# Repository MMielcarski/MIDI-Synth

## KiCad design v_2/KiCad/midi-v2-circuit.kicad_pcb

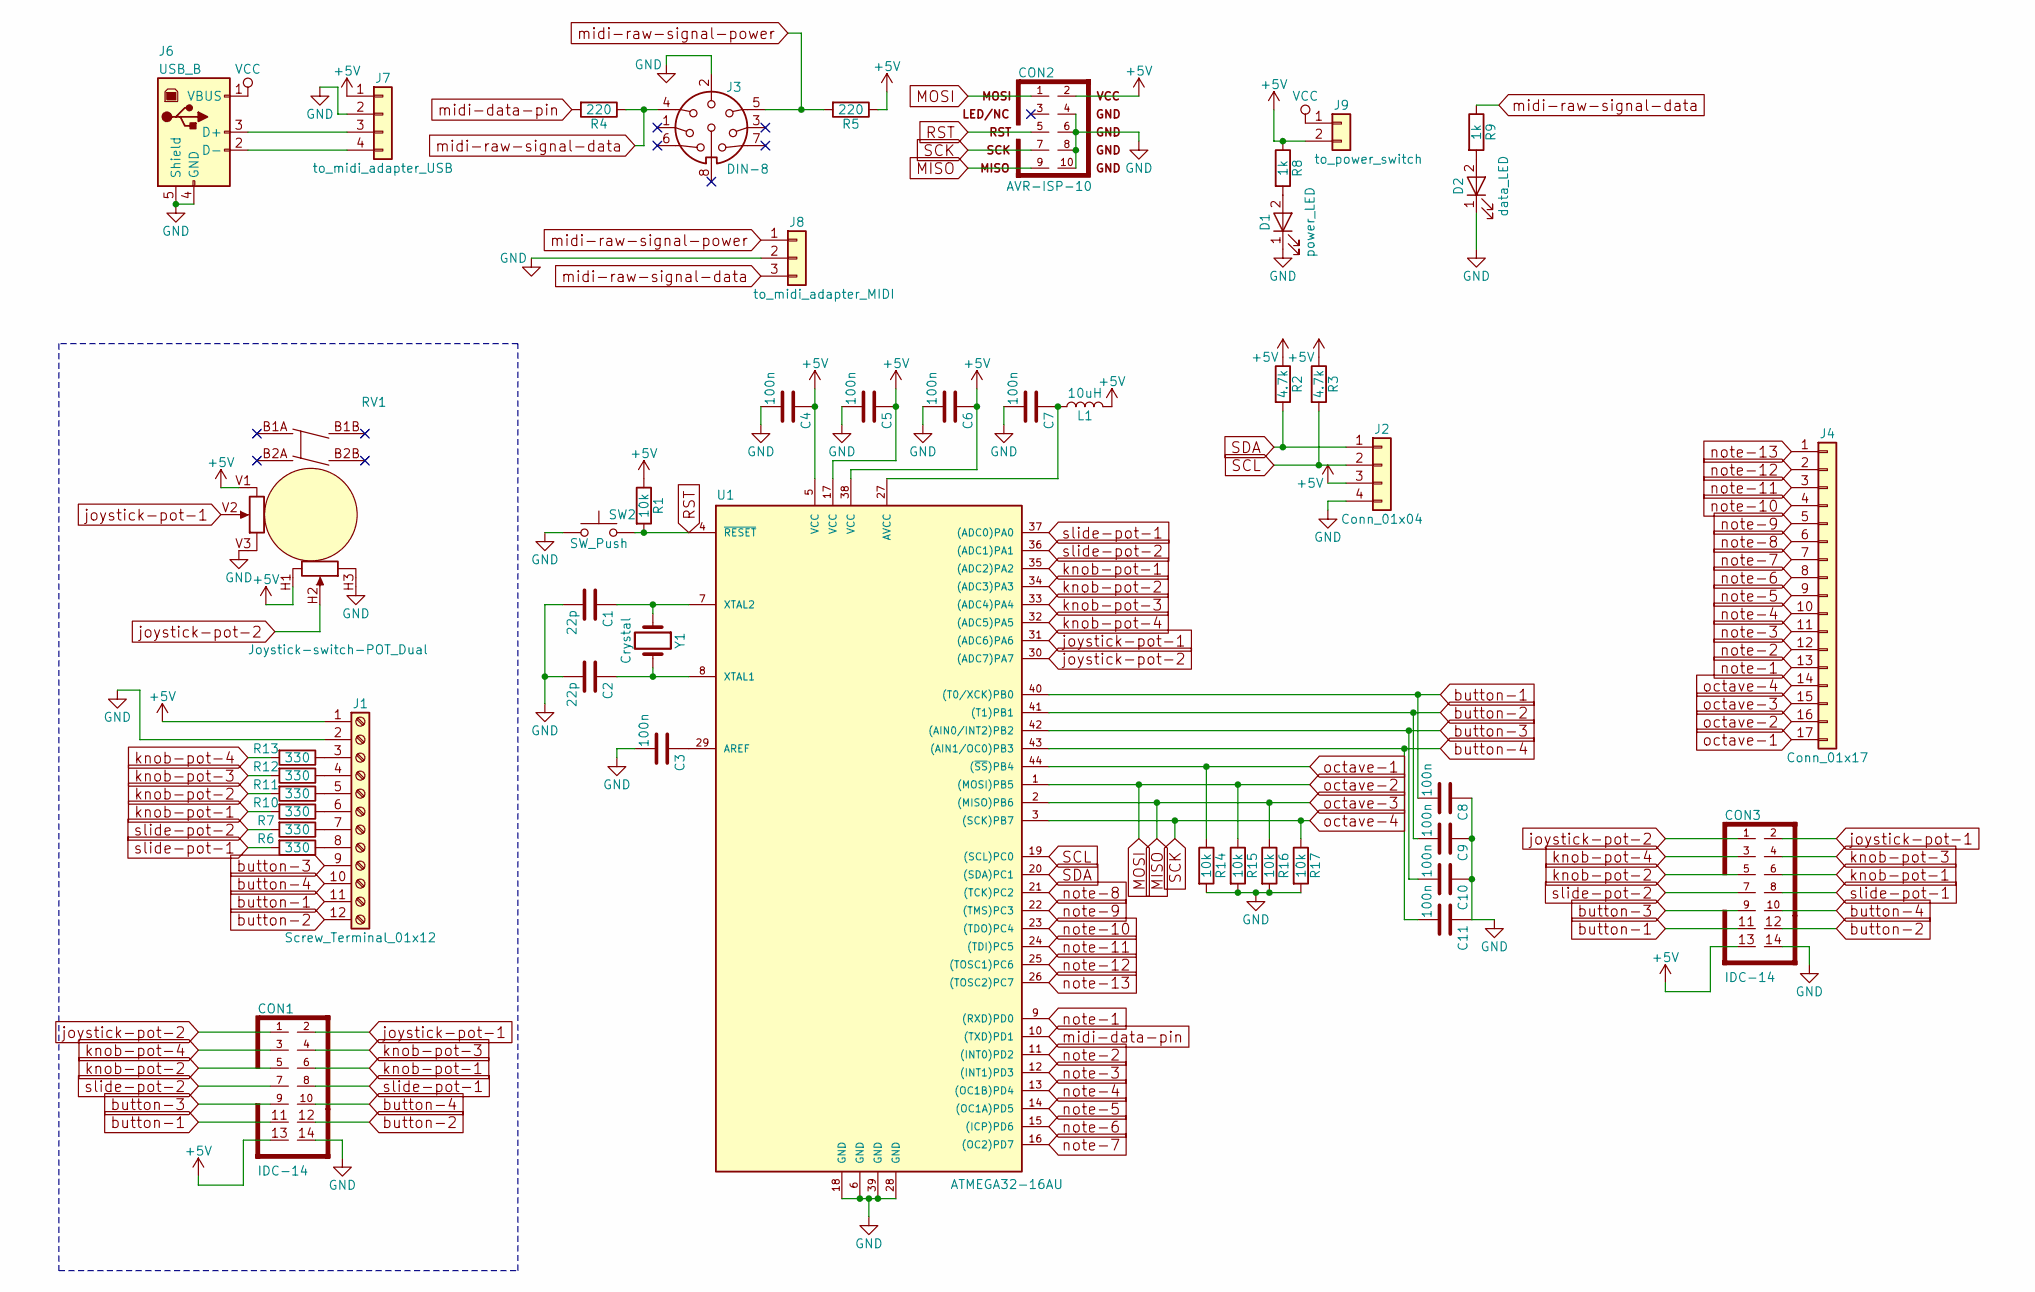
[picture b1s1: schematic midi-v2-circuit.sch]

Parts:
C1, C2: 22p; C_0805_HandSoldering
C3, C4, C5, C6, C7, C8, C9, C10, C11: 100n; C_0805_HandSoldering
CON1: IDC-14; IDC-Header_2x07_Pitch2.54mm_Angled
CON2: AVR-ISP-10; IDC-Header_2x05_Pitch2.54mm_Angled
CON3: IDC-14; IDC-Header_2x07_Pitch2.54mm_Straight
D1: power_LED; LED_D3.0mm
D2: data_LED; LED_D3.0mm
J1: Screw_Terminal_01x12; TerminalBlock_Phoenix_MPT-2.54mm_12pol
J2: Conn_01x04; Pin_Header_Straight_1x04_Pitch2.54mm
J3: DIN-8; MIDI-DIN-8
J4: Conn_01x17; IDC-Header_2x10_Pitch2.54mm_Angled
J6: USB_B
J7: to_midi_adapter_USB; Pin_Header_Straight_1x04_Pitch2.54mm
J8: to_midi_adapter_MIDI; Pin_Header_Straight_1x03_Pitch2.54mm
J9: to_power_switch; Pin_Header_Straight_1x02_Pitch2.54mm
L1: 10uH; L_0805_HandSoldering
R1, R14, R15, R16, R17: 10k; R_0805_HandSoldering
R2, R3: 4.7k; R_0805_HandSoldering
R4, R5: 220; R_0805_HandSoldering
R6, R7, R10, R11, R12, R13: 330; R_0805_HandSoldering
R8, R9: 1k; R_0805_HandSoldering
RV1: Joystick-switch-POT_Dual; JOYSTICK
SW2: SW_Push; SW_Tactile_Straight_KSA0Axx1LFTR
U1: ATMEGA32-16AU; LQFP-44_10x10mm_Pitch0.8mm
Y1: Crystal; Crystal_HC18-U_Vertical

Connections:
+5V: C4.1, C5.1, C6.1, CON1.13, CON2.2, CON3.13, J1.1, J2.3, J7.1, J9.2, L1.2, R1.1, R2.1, R3.1, R5.1, R8.1, RV1.H1, RV1.V1, U1.5 (VCC), U1.17 (VCC), U1.38 (VCC)
GND: C1.2, C2.2, C3.2, C4.2, C5.2, C6.2, C7.2, C8.1, C9.1, C10.1, C11.1, CON1.14, CON2.4, CON2.6, CON2.8, CON2.10, CON3.14, D1.1 (K), D2.1 (K), J1.2, J2.4, J3.2, J6.4 (GND), J6.5 (Shield), J7.2, J8.2, R14.2, R15.2, R16.2, R17.2, RV1.H3, RV1.V3, SW2.1, U1.6 (GND), U1.18 (GND), U1.28 (GND), U1.39 (GND)
MISO: CON2.9, J4.15, R16.1, U1.2 ((MISO)PB6)
MOSI: CON2.1, J4.16, R15.1, U1.1 ((MOSI)PB5)
unnamed: C1.1, U1.7 (XTAL2), Y1.1
unnamed: C2.1, U1.8 (XTAL1), Y1.2
unnamed: C3.1, U1.29 (AREF)
unnamed: C7.1, L1.1, U1.27 (AVCC)
unnamed: D1.2 (A), R8.2
unnamed: D2.2 (A), R9.2
unnamed: J1.3, R13.1
unnamed: J1.4, R12.1
unnamed: J1.5, R11.1
unnamed: J1.6, R10.1
unnamed: J1.7, R7.1
unnamed: J1.8, R6.1
unnamed: J6.2 (D-), J7.4
unnamed: J6.3 (D+), J7.3
RST: CON2.5, R1.2, SW2.2, U1.4 (~RESET)
SCK: CON2.7, J4.14, R17.1, U1.3 ((SCK)PB7)
SCL: J2.2, R3.2, U1.19 ((SCL)PC0)
SDA: J2.1, R2.2, U1.20 ((SDA)PC1)
VCC: J6.1 (VBUS), J9.1
button-1: C8.2, CON1.11, CON3.11, J1.11, U1.40 ((T0/XCK)PB0)
button-2: C9.2, CON1.12, CON3.12, J1.12, U1.41 ((T1)PB1)
button-3: C10.2, CON1.9, CON3.9, J1.9, U1.42 ((AIN0/INT2)PB2)
button-4: C11.2, CON1.10, CON3.10, J1.10, U1.43 ((AIN1/OC0)PB3)
joystick-pot-1: CON1.2, CON3.2, RV1.V2, U1.31 ((ADC6)PA6)
joystick-pot-2: CON1.1, CON3.1, RV1.H2, U1.30 ((ADC7)PA7)
knob-pot-1: CON1.6, CON3.6, R10.2, U1.35 ((ADC2)PA2)
knob-pot-2: CON1.5, CON3.5, R11.2, U1.34 ((ADC3)PA3)
knob-pot-3: CON1.4, CON3.4, R12.2, U1.33 ((ADC4)PA4)
knob-pot-4: CON1.3, CON3.3, R13.2, U1.32 ((ADC5)PA5)
midi-data-pin: R4.2, U1.10 ((TXD)PD1)
midi-raw-signal-data: J3.4, J8.3, R4.1, R9.1
midi-raw-signal-power: J3.5, J8.1, R5.2
note-1: J4.13, U1.9 ((RXD)PD0)
note-2: J4.12, U1.11 ((INT0)PD2)
note-3: J4.11, U1.12 ((INT1)PD3)
note-4: J4.10, U1.13 ((OC1B)PD4)
note-5: J4.9, U1.14 ((OC1A)PD5)
note-6: J4.8, U1.15 ((ICP)PD6)
note-7: J4.7, U1.16 ((OC2)PD7)
note-8: J4.6, U1.21 ((TCK)PC2)
note-9: J4.5, U1.22 ((TMS)PC3)
note-10: J4.4, U1.23 ((TDO)PC4)
note-11: J4.3, U1.24 ((TDI)PC5)
note-12: J4.2, U1.25 ((TOSC1)PC6)
note-13: J4.1, U1.26 ((TOSC2)PC7)
octave-1: J4.17, R14.1, U1.44 ((~SS~)PB4)
slide-pot-1: CON1.8, CON3.8, R6.2, U1.37 ((ADC0)PA0)
slide-pot-2: CON1.7, CON3.7, R7.2, U1.36 ((ADC1)PA1)

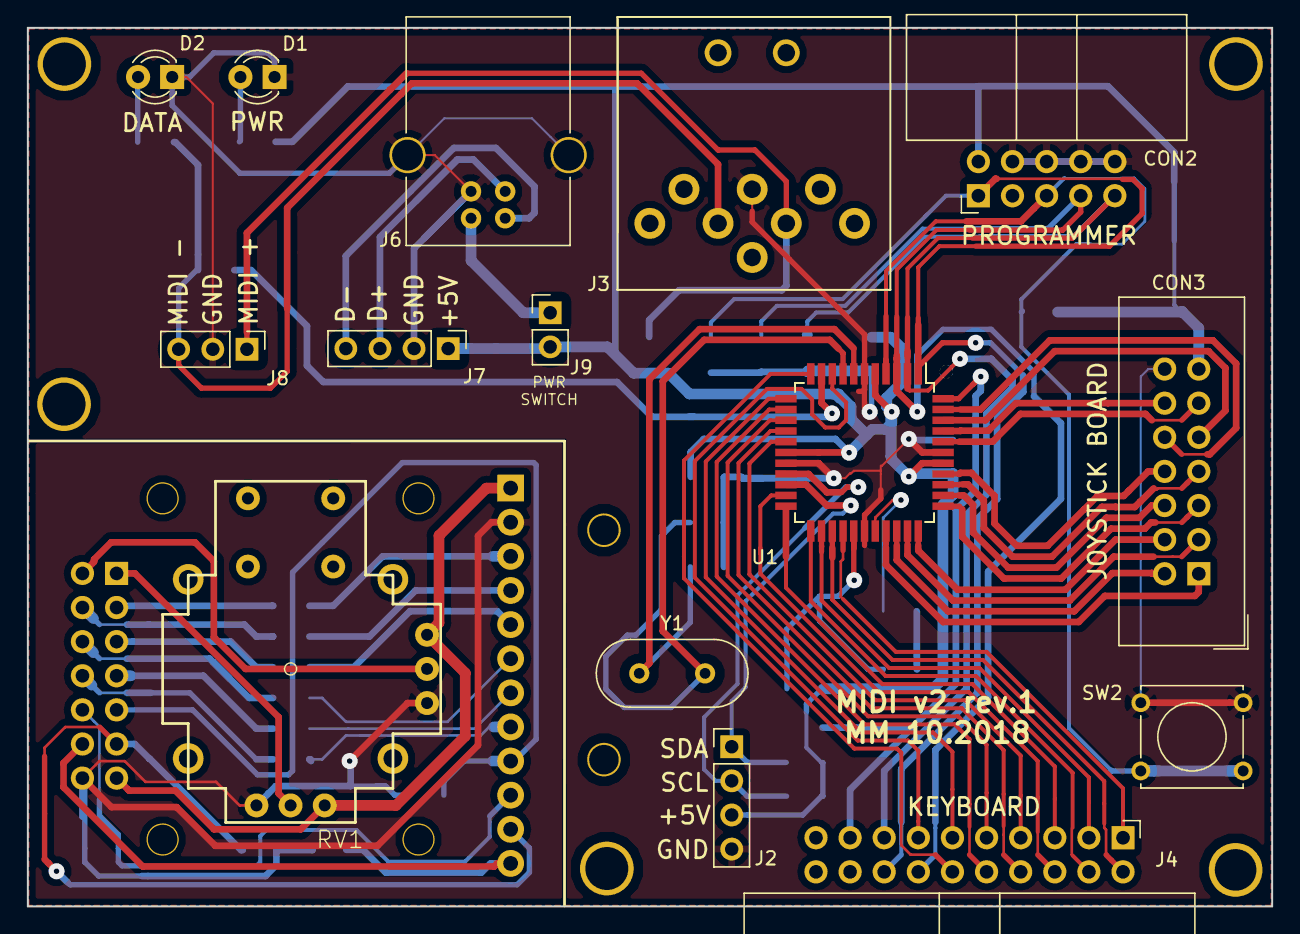
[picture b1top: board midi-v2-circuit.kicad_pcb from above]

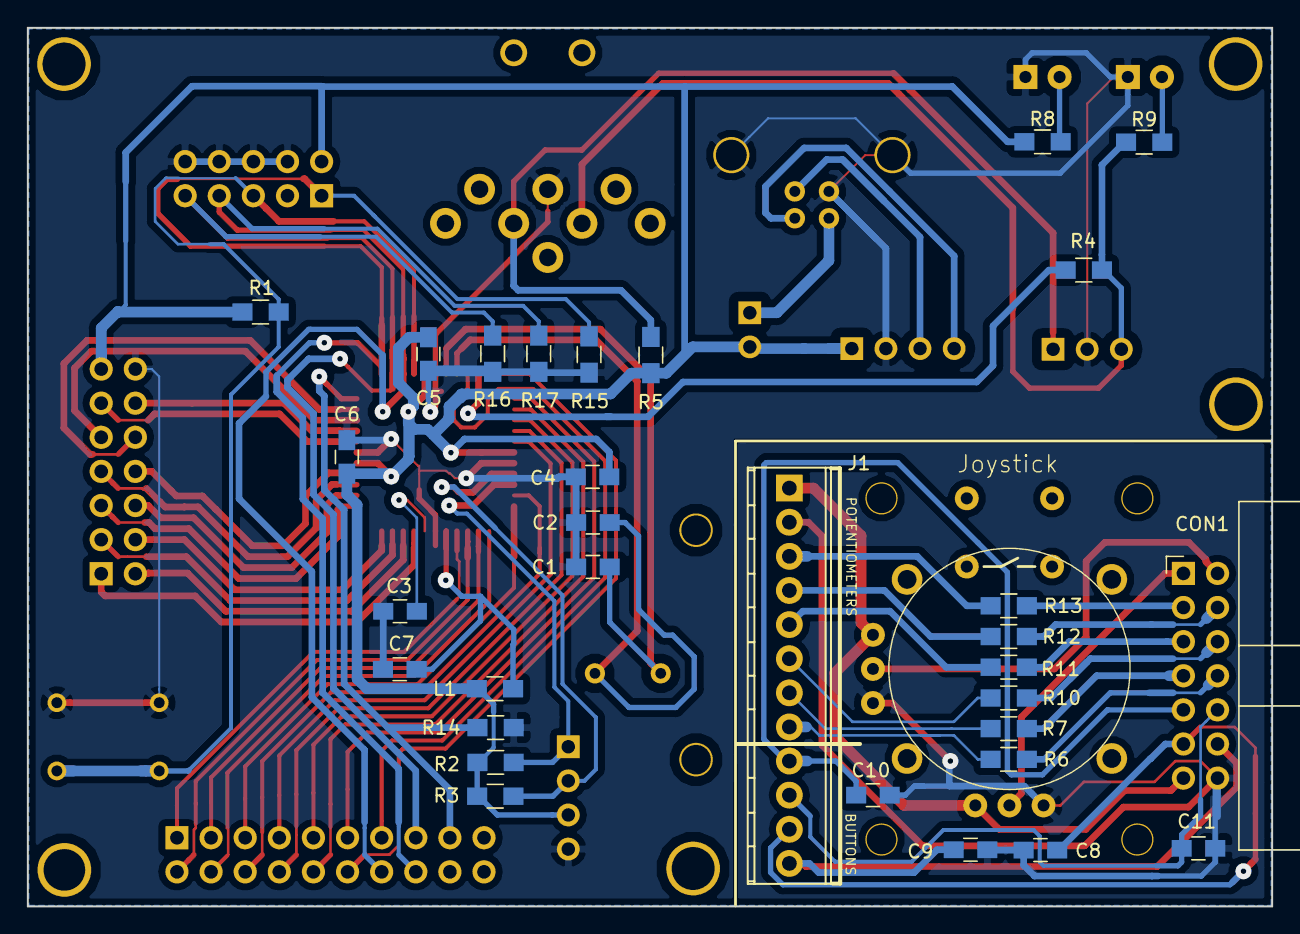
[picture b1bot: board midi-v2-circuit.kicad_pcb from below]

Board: 2 copper layers, 92.6 x 65.4 mm, 46 parts (32 on the bottom side), 52 nets.

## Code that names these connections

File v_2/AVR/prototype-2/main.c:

// device: 	AtMega 32
// author:  Maciej Mielcarski
// Midi v2

#define F_CPU 16000000UL
#include <avr/io.h>
#include <avr/interrupt.h>
//#define BAUD 9600 
#define BAUD 31250
#define MYUBRR F_CPU/16/BAUD-1	// ubrr = 31(MIDI) 113(9600) normal asynch. mode
#include <util/setbaud.h>
#define TIM1_PSC 1024		// TIMER 1 prescaler value
#define TIM1_PER 10		// TIMER 1 desired period in miliseconds

#define NOTE_ON_CMD 0x90
#define NOTE_OFF_CMD 0x80
#define CC_CMD 0xB0

#define PITCH_BEND_CMD 0xE0
#define MODULATION_WHEEL_CMD 0x01
#define BREATH_CONTROLLER_CMD 0x02
#define MAIN_VOLUME_CMD 0x07	
#define GEN_PURP_CTRL_1_CMD 0x10
#define GEN_PURP_CTRL_2_CMD 0x11
#define GEN_PURP_CTRL_3_CMD 0x12
#define GEN_PURP_CTRL_4_CMD 0x13

#define SOUND_CTRL_6_DECAY_CMD 0x4B

#define VEL_DEF_CMD		0x40	// default 64 velocity

#define UNDEF_1 0x14
#define UNDEF_2 0x15
#define UNDEF_3 0x16
#define UNDEF_4 0x17
#define UNDEF_5 0x18
#define UNDEF_6 0x19
#define UNDEF_7 0x1A
#define UNDEF_8 0x19

#define CC_ON_VAL 0x46
#define CC_OFF_VAL 0x3C

#define note1 PD0 
#define note2 PD2 
#define note3 PD3 
#define note4 PD4 
#define note5 PD5 
#define note6 PD6 
#define note7 PD7 
#define note8 PC2 
#define note9 PC3 
#define note10 PC4 
#define note11 PC5 
#define note12 PC6 
#define note13 PC7 

#define octave1 PB4 
#define octave2 PB5 
#define octave3 PB6 
#define octave4 PB7 

#define button_pin_port PINB 
#define button1 PB0
#define button2 PB1
#define button3 PB2
#define button4 PB3

int NOTES_tab[13] = {note1,note2,note3,note4,note5,note6,note7,note8,note9,note10,note11,note12,note13};
int OCTAVES_tab[4] = {octave1,octave2,octave3,octave4};
int PRESSED_KEY_tab[13][4]={0};

int BUTTON_tab = {button1, button2, button3, button4};
int PRESSED_BUTTON_tab[4] = {};
unsigned int PRESSED_BUTTON_STATE_tab[4] = {};

int adc_read[8] = {};
int adc_prev_read[8] = {};	

const float EMA_a = 0.6;
int EMA[8] = {};
int EMA_prev[8] = {};

int octave_change = 3;

// ------------------------- TIMER ----------------------------------------
void TIM1_Init(void)	// enable interrupts
{
    OCR1A = (((F_CPU/1000) / TIM1_PSC) * TIM1_PER) - 1;	// counter size
    TCCR1B |= (1 << WGM12);							// Mode 4, CTC on OCR1A
    TIMSK |= (1 << OCIE1A);						// Set interrupt on compare match	
    TCCR1B |= (1 << CS12) | (1 << CS10);			// set prescaler to 1024 and start the timer
    sei();	
}

// ------------------------- USART ----------------------------------------
void USART_Init(unsigned int ubrr)		
{
   UBRRH = (unsigned char)(ubrr>>8);	// set baud rate to 31250
   UBRRL = (unsigned char)ubrr;		//
   UCSRB = (1<<TXEN);		// Enable transmitter 
   UCSRC = (1<<URSEL)|(1<<USBS)|(3<<UCSZ0);		// Set frame format: 8data, 2stop bit
}

void uart_putchar(char c) 
{
	while ( !(UCSRA & (1<<UDRE)) )	// Wait for empty transmit buffer 
	;
    UDR = c;							// Put data into buffer, sends the data 
}

void uart_putstring(char tab[])
{
	int i =0;
	while (( UCSRA & (1<<UDRE))  == 0){};
        while (tab[i] != 0x00)
		{ 
            uart_putchar(tab[i]);
			i++; 
        }
}

void uart_putint(int value)
{
	char tab[16];
	itoa(value,tab,10);
	uart_putstring(tab);
}

// ------------------------- ADC ----------------------------------------
void ADC_Init(void)
{
	ADCSRA |= (1 << ADPS2) | (1 << ADPS1) | (1 << ADPS0); // Set ADC prescaler to 128 - 125KHz sample rate @ 16MHz
	ADMUX |= (1 << REFS0); 	// Set ADC reference to AVCC
	ADCSRA |= (1 << ADEN);  // Enable ADC
}

uint16_t ADC_read(uint8_t channel)		
{
	channel &= 0x07;					// AND operation with 7 (will keep channel between 0-7) 
	ADMUX = (ADMUX & 0xF8) | channel;	// clears 3 first bits before OR
	ADCSRA |= (1 << ADSC);				// start single convesrion
	while(ADCSRA & (1 << ADSC));		// wait for conversion to complete
	return ADCW;
}
// ------------------------- OTHER ----------------------------------------

void PORT_Init(void)
{
	MCUCSR = (1<<JTD);			//disabling JTAG
	MCUCSR = (1<<JTD);			//
	DDRD = 0xFF;
	DDRC = 0xFF;
	
	PORTB |= (1<<button1)|(1<<button2)|(1<<button3)|(1<<button4);	// pull-up on buttons
}

void note_on(int key, int oct)
{
	uart_putchar(NOTE_ON_CMD);		// note on
	uart_putchar(key + (oct+octave_change) * 12);
	uart_putchar(VEL_DEF_CMD);
}

void note_off(int key, int oct)
{
	uart_putchar(NOTE_OFF_CMD);		// note off
	uart_putchar(key + (oct+octave_change) * 12);
	uart_putchar(VEL_DEF_CMD);
}

int button_pressed(int pin_port, int pin)
{
	if(!(pin_port & (1<<pin)) )
		return 1;
	else 
		return 0;
}

void CC_send_BUTTON(uint8_t data1, uint8_t data2, int button_pin)
{
	if(button_pressed(button_pin_port,button_pin) && !(PRESSED_BUTTON_tab[button_pin]))
	{
		PRESSED_BUTTON_tab[button_pin] = 1;
		uart_putchar(CC_CMD);
		if(PRESSED_BUTTON_STATE_tab[button_pin])
		{
			PRESSED_BUTTON_STATE_tab[button_pin] = 0;
			uart_putchar(data1);		
			uart_putchar(CC_OFF_VAL);	
		}
		else
		{
			PRESSED_BUTTON_STATE_tab[button_pin] = 1;
			uart_putchar(data1);		
			uart_putchar(CC_ON_VAL);
		}	
	}
	else if(!(button_pressed(button_pin_port,button_pin)))
	{
		PRESSED_BUTTON_tab[button_pin] = 0;
	}
}

void CC_send_ADC(uint8_t control_num,  unsigned int channel)
{
	adc_prev_read[channel] = adc_read[channel];
	int adc_sum = 0;
	for(int i=0;i<16;i++)
	{
		adc_sum += ADC_read(channel);
	}
	adc_read[channel] = adc_sum/16;

	uint8_t adc_7bit = (adc_read[channel] >> 3);
	uint8_t adc_prev_7bit = (adc_prev_read[channel] >> 3);

	if((int)adc_7bit != (int)adc_prev_7bit)
	{
		EMA_prev[channel] = EMA[channel];
		EMA[channel] = (EMA_a*adc_7bit) + (1-EMA_a)*adc_prev_7bit;
		if(EMA[channel] != EMA_prev[channel])
		{
			uart_putchar(CC_CMD);
			uart_putchar(control_num);
			uart_putchar(EMA[channel]);
		}
	}
}

ISR(TIMER1_COMPA_vect)	// timer1 overflow interrupt
{
		CC_send_BUTTON(UNDEF_1,1,button1);	// todo: tab with pin numbers
		CC_send_BUTTON(UNDEF_2,1,button2);
		CC_send_BUTTON(UNDEF_3,1,button3);
		CC_send_BUTTON(UNDEF_4,1,button4);

	// octave change:
	/*if(button_pressed(button_pin_port,button3) && !(PRESSED_BUTTON_tab[button3]))
	{
		octave_change++;
	}
	else if(!(button_pressed(button_pin_port,button3)))
	{
		PRESSED_BUTTON_tab[button3] = 0;
	}

	if(button_pressed(button_pin_port,button4) && !(PRESSED_BUTTON_tab[button4]))
	{
		if(octave_change > 0)
		octave_change--;
	}
	else if(!(button_pressed(button_pin_port,button4)))
	{
		PRESSED_BUTTON_tab[button4] = 0;
	}*/

		CC_send_ADC(UNDEF_5, 0);	// slide 1
		CC_send_ADC(UNDEF_6, 1);	// slide 2
		CC_send_ADC(GEN_PURP_CTRL_1_CMD, 2);	// knob 1 
		CC_send_ADC(GEN_PURP_CTRL_2_CMD, 3);	// knob 2
		CC_send_ADC(GEN_PURP_CTRL_3_CMD, 4);	// knob 3
		CC_send_ADC(GEN_PURP_CTRL_4_CMD, 5);	// knob 4		
		CC_send_ADC(UNDEF_7, 6);	// joystick 1	
		CC_send_ADC(UNDEF_8, 7);	// joystick 2	

for(int i=0; i<13; i++)		// notes loop
		{
			if(i < 7)	// PORTD
			{
				PORTD |= (1<<NOTES_tab[i]);
			}
			else		// PORTC
			{
				PORTC |= (1<<NOTES_tab[i]);
			}

			// if(i == 12)		// last key case
			// {
			// 	if(PINC & (1<<NOTES_tab[12]) && !(PRESSED_KEY_tab[12][0]) )
			// 	{
			// 		PRESSED_KEY_tab[12][0] = 1;
			// 		note_on(12,0);
			// 	}
			// 	else if( !(PINC & (1<<NOTES_tab[12])) && PRESSED_KEY_tab[12][0])
			// 	{
			// 		PRESSED_KEY_tab[12][0] = 0;
			// 		note_off(12,0);
			// 	}
			// }

			for(int j=0; j<4; j++)		// octaves loop
			{
				if( PINB & (1<<OCTAVES_tab[j]) && !(PRESSED_KEY_tab[i][j]) )
				{
					PRESSED_KEY_tab[i][j] = 1;
					note_on(i,j);
				}
				else if( !(PINB & (1<<OCTAVES_tab[j])) && PRESSED_KEY_tab[i][j] )
				{
					PRESSED_KEY_tab[i][j] = 0;
					note_off(i,j);
				}
			}
			
			if(i < 7)	// PORTD
			{
				PORTD &= ~(1<<NOTES_tab[i]);
			}
			else		// PORT C
			{
				PORTC &= ~(1<<NOTES_tab[i]);
			}
		}
}

// ------------------------- MAIN ----------------------------------------

int main(void)
{
	USART_Init(MYUBRR);
	PORT_Init();
	ADC_Init();
	TIM1_Init();

	while(1)
	{

	}
}

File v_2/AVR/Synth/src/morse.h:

#ifndef MORSE_H_
#define MORSE_H_

#define F_CPU 1000000UL
#include <avr/io.h>
#include "HD44780.h"
#include <util/delay.h>
#include <stdio.h>
#include <stdlib.h> 
#include <avr/interrupt.h>

#define ENC_BTN PA3
#define ENC_A PA1
#define ENC_B PA2
#define LED PC4
#define SW_1 PC1
#define SW_2 PC2

	extern int encoderCount;	//encoder turns
	extern uint8_t val;			//encoder actual gray code reading
	extern int asciiNum;		//ascii value of currently displayed character
	extern char userInput[];
	extern volatile uint16_t Timer1, Timer2;
	extern int flag;

	void delay_ms( int ms);
	uint8_t readEncoder(void);
	void initializeSetup (void);
	void readEncoderCounter (void);
	void broadcast(int period,int length);
	void LCD_clearLine(int nr);
	int dial(void);
	void messageDisplay(void);
	int isButton(void);
	void LCD_move(char dir);
	void LCD_moveMode(void);
	void blinkLed(int on, int off);
	int messageDecrypt(void);
	int setWpmSpeed(void);

	/*typedef struct {
		volatile uint8_t *pin;
		uint8_t keyMask;
		uint8_t waitTime;
		uint8_t flag;
		int isPressed(void);
	}BUTTON;*/

#endif /* MORSE_H_ */

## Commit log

2018-06-24 version 2 development start
2018-06-25 ready for atmega 90 deg rotate branch
2018-06-25 rotation done, design stable enough for merging
2018-06-25 autosave file update
2018-06-27 pcb first version complete - ready for hardware check and further optimalisation do 10x10cm
2018-07-08 adc first success
2018-10-03 improvements before first pcb order
2018-10-03 tweaks before first order part 2
2018-10-10 clearence changed to min 0.3 mm, resistor placement tweaks, ready for fabrication
2018-10-11 further tweaks, ready to order
2018-10-12 resized to max 10x10cm - ordering at JLCPCB
2018-10-18 aux files recovery
2018-11-09 prototyping ordered PCB, USART working, problem with keyboard keys
2018-11-11 keyboard works without last key, proceeding to test ADC
2018-11-11 ADC working
2018-11-12 Basic MIDI completed (sending corresponding note on/off)
2018-11-17 keyboard and potentiomaters MIDI commands working, problem with ADC reading noise from PC power supply (perfect reading with battery supply)
2018-11-25 all pots working properly without noise, buttons work on rising edge, changed to classic NO pushbuttons, midi ready for polishing
2018-12-08 splitted code into modules and headers, added midi state toggling for buttons; working
2018-12-08 quick midi cmd number fix
2019-01-15 product finished
